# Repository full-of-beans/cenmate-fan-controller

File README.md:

# CENMATE 6-Bay HDD Enclosure Fan Controller

Custom cooling and power-monitoring controller for a **CENMATE six-bay USB HDD enclosure (JBOD/DAS)**.

> **CMFC001 prototype boards ordered (2026-11-20).** This is an engineering prototype, not a qualified assembled product. See [hardware revision register](docs/hardware-revisions.md) for the immutable KiCad/manufacturing source and order status.

## Current design

- **Controller:** Seeed Studio XIAO RP2350, powered from the enclosure's USB-A 5 V supply through its USB-C connector. Fan 12 V switching is controlled separately by the enclosure rocker via J5 and Q3, not by USB availability.
- **Fans:** Two independently controlled 12 V, four-wire PWM fans, with separate PWM drive and tachometer inputs. The intended physical fan headers are [MODDIY 2.54 mm right-angle 4-pin male fan connectors](https://www.moddiy.com/products/5408/4-Pin-3-Pin-2.54mm-Pitch-2510-Fan-Male-Angled-Connector-Black.html). **The PCB still uses Molex right-angle header footprints/3D models as placeholders; the MODDIY parts have not been physically verified against those holes or pin orientation.** Do not purchase/install the Molex parts based on the current CAD representation.
- **Fan power:** DMP3056L-7 P-channel MOSFET switches the 12 V fan branch; its gate is controlled by the enclosure rocker via J5 and defaults off if the switch lead opens. PWM duty mapping and safe startup/reset behavior require firmware and bench verification.
- **Temperature sensing:** Two on-board 10 kΩ NTC thermistors, each read on its own XIAO ADC input through a 10 kΩ pull-up.
- **Current monitor:** TI INA228 on I²C, sensing the HDD backplane's positive 12 V feed through a **1 mΩ Bourns shunt**. The fan supply branches before the shunt, so the shunt measures the HDD branch rather than fan current. Accuracy and Kelvin/landing resistance must be checked by calibration.
- **HDD power path:** Center-positive 12 V barrel input **J1** → shunt **RSH1** → Phoenix Contact two-position screw terminal **J2** → HDD enclosure. **J2 pin 1 = +12 V, pin 2 = GND.** The PCB has explicit `12V` and `GND` silkscreen markings beside J2; verify wiring polarity before connection.
- **Grounding:** Common system ground, with a two-layer PCB and ground copper fill.

The enclosure's power brick is labeled **12 V / 9 A**. The selected **Tensility 54-00286 barrel jack is rated 7 A**; the owner has explicitly accepted the prototype risk rather than replacing it. This does **not** establish that six-drive startup and operating loads meet the connector rating. Measure the actual current, contact voltage drop, and connector heating during controlled bring-up.

## Hardware and mechanical status

The board and custom backplate have been checked for fit by the owner in Onshape. This does not independently verify fabricated edge reliefs, actual mated MODDIY header geometry, cable bends, or as-built tolerances. Check physical fit before connecting the HDD enclosure.

The CMFC001 prototype PCB was ordered from JLCPCB as **25 bare 30 × 80 mm, two-layer, 1.6 mm FR-4, 1 oz copper, green-mask, lead-free HASL boards**, plus one top-side paste stencil (JLCPCB order `W2026112104450984`). Actual manufactured fit, CAM interpretation, and assembly remain to be checked when boards arrive.

## Repository layout

```text
hardware/
  fan-controller.kicad_pro   KiCad 10 project
  fan-controller.kicad_sch   Current controller schematic
  fan-controller.kicad_pcb   Current PCB layout
  fan-controller.kicad_dru   Custom DRC rules
  libraries/                 Project-local symbols, footprints, and models
firmware/                   Pico SDK firmware and native tests
docs/                       Circuit design and hardware revision records
mechanical/                 Mechanical files (as available)
```

Open `hardware/fan-controller.kicad_pro` with **KiCad 10**. The project-local `FanController` libraries must resolve before editing or plotting.

## Ordered prototype and validation

CMFC001 manufacturing identity, source commit and archive path are recorded in [hardware revisions](docs/hardware-revisions.md). Do not regenerate the ordered ZIP as part of documentation cleanup.

Before connecting drives, perform continuity and polarity checks, current-limited initial power-up, USB/12 V power sequencing, fan enable/PWM/tach tests, INA228 communication and calibration, and thermistor checks. Only then test with the enclosure under controlled startup/full-load conditions while monitoring the accepted 7 A connector risk.

## Firmware design status

Phase 1 adds USB configuration and telemetry, persistent independent FIXED PWM, electrical and rear-plenum sensing, and AUTO diagnostics and protective cooling. Factory AUTO uses 100% duty while the cooling model is uncalibrated. FIXED has no automatic cooling overrides and remains active at the selected duty if the host disconnects. Assembled hardware and autonomous thermal behavior await bench validation.

- [Firmware architecture and verified CAD pin mapping](docs/software-architecture.md)
- [Build, flash, bring-up and characterization](docs/hardware-bringup.md)
- [USB CDC protocol](docs/usb-protocol.md)
- [Configuration schema and persistence](docs/firmware-configuration.md)

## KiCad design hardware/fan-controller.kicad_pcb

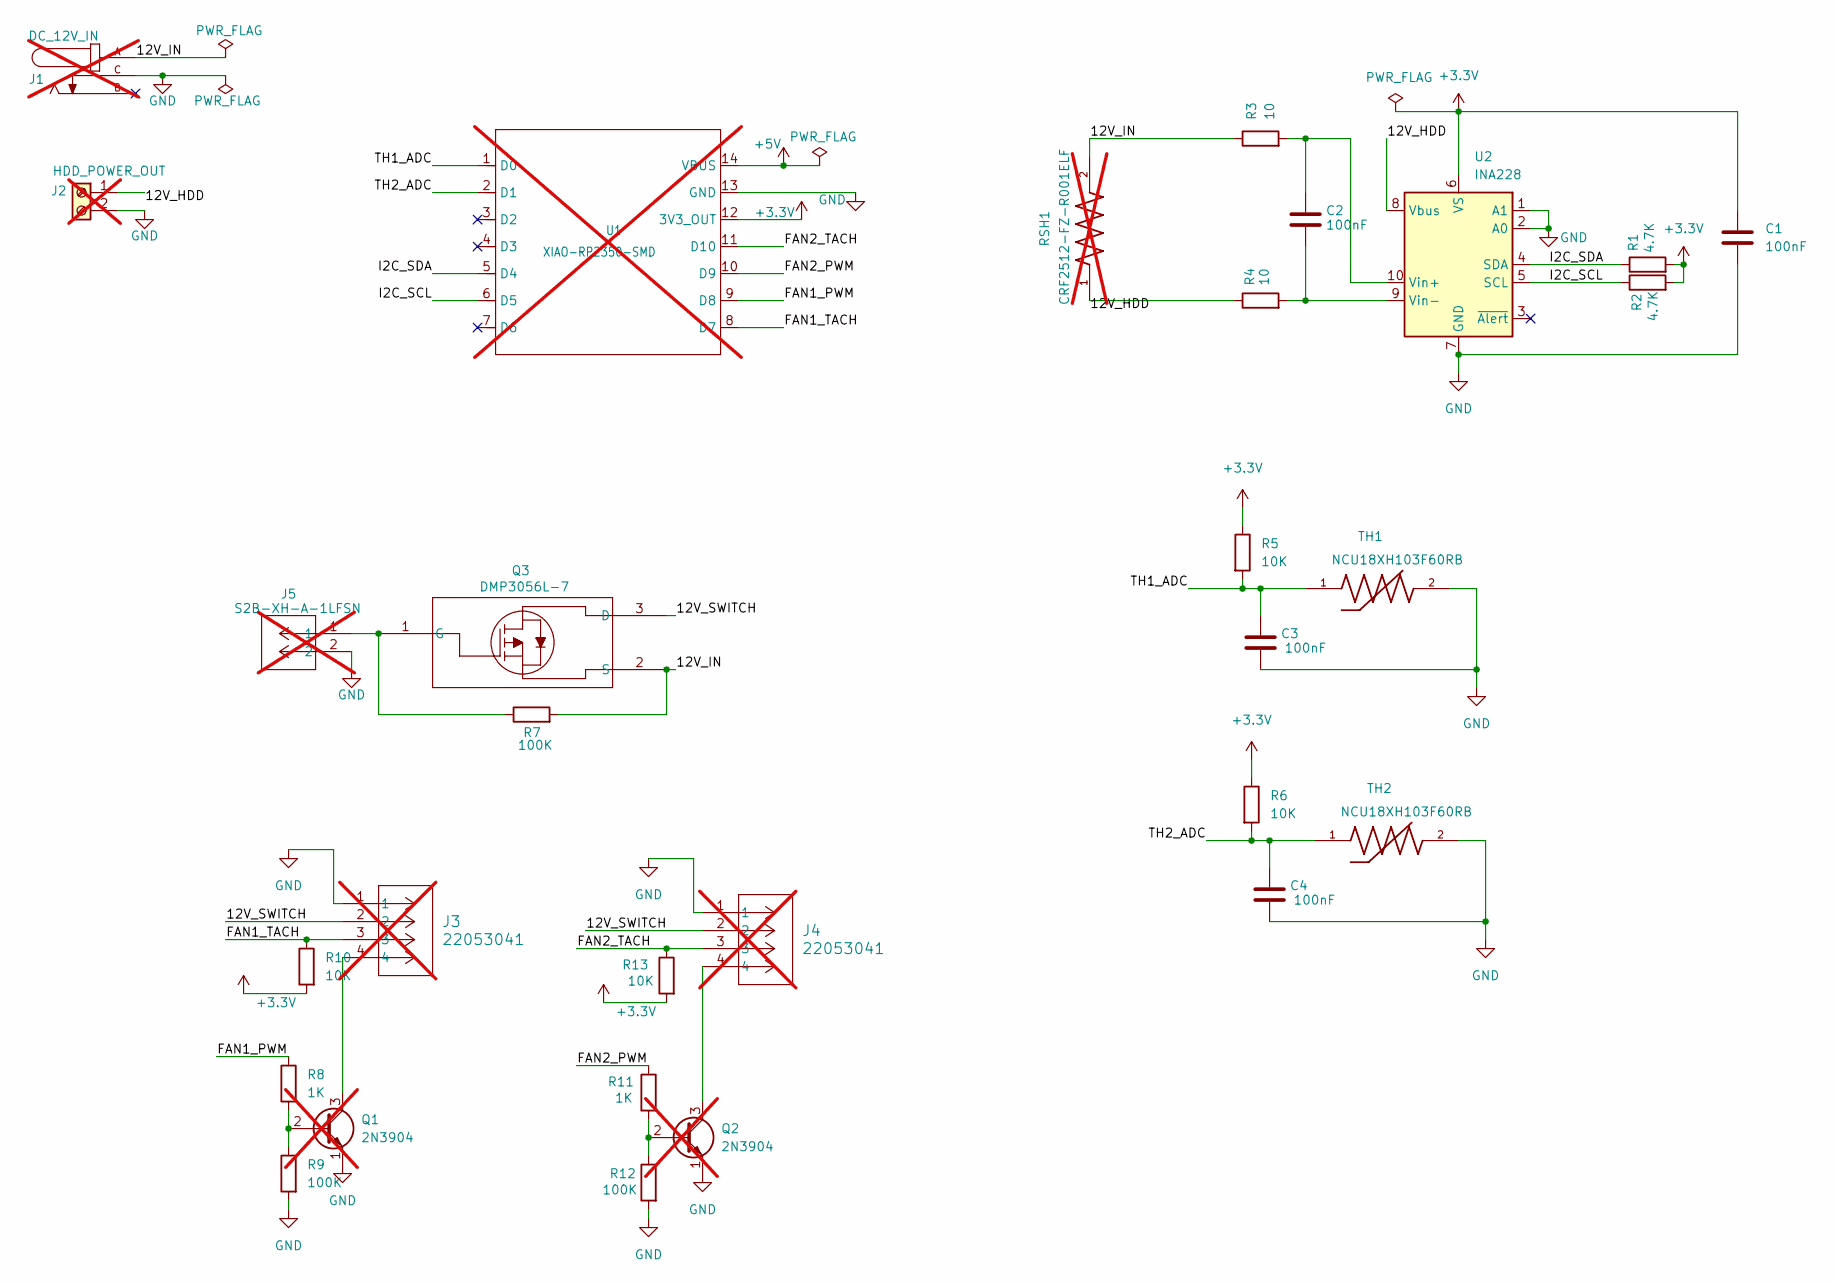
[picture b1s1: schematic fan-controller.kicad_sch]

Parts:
C1, C2, C3, C4: 100nF; C_0805_2012Metric; MPN CL21B104KACNFNC; DigiKey_PN 1276-2442-1-ND
J1: DC_12V_IN; TENSILITY_54-00286; MPN 54-00286; DigiKey_PN 839-54-00286-ND; not fitted
J2: HDD_POWER_OUT; PHOENIX_5442206; MPN 5442206; DigiKey_PN 277-12547-ND; not fitted
J3, J4: 22053041; CONN_A-7478-04A_MOL; MPN 0022053041; DigiKey_PN WM4302-ND; not fitted
J5: S2B-XH-A-1LFSN; CONN_S2B-XH-A-1LFSN_JST; MPN S2B-XH-A-1(LF)(SN); not fitted
Q1, Q2: 2N3904; TO-92_Inline; MPN 2N3904BU; DigiKey_PN 2N3904FS-ND; not fitted
Q3: DMP3056L-7; DIODE3_DESD1CAN2SOQ-7_DIO; MPN DMP3056L-7; DigiKey_PN DMP3056L-7DICT-ND
R1, R2: 4.7K; R_0805_2012Metric; MPN RC0805FR-074K7L; DigiKey_PN 311-4.70KCRCT-ND
R3, R4: 10; R_0805_2012Metric; MPN RC0805FR-0710RL; DigiKey_PN 311-10.0CRCT-ND
R5, R6, R10, R13: 10K; R_0805_2012Metric; MPN RC0805FR-0710KL; DigiKey_PN 311-10.0KCRCT-ND
R7, R9, R12: 100K; R_0805_2012Metric; MPN RC0805FR-07100KL; DigiKey_PN 311-100KCRCT-ND
R8, R11: 1K; R_0805_2012Metric; MPN RC0805FR-071KL; DigiKey_PN 311-1.00KCRCT-ND
RSH1: CRF2512-FZ-R001ELF; RESC6432X80N; MPN CRF2512-FZ-R001ELF; DigiKey_PN CRF2512-FZ-R001ELFCT-ND; not fitted
TH1, TH2: NCU18XH103F60RB; THRMC1608X95N; MPN NCU18XH103F60RB; DigiKey_PN 490-16279-1-ND
U1: XIAO-RP2350-SMD; XIAO-RP2350-no-underside; MPN 102010550; DigiKey_PN 1597-102010550-ND; not fitted
U2: INA228; TSSOP-10_3x3mm_P0.5mm; MPN INA228AIDGSR; DigiKey_PN 296-INA228AIDGSRCT-ND

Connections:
+3.3V: C1.1, R1.2, R2.2, R5.1, R6.1, R10.2, R13.2, U1.12 (3V3_OUT), U2.6 (VS)
+5V: U1.14 (VBUS)
/12V_HDD: J2.1, R4.1, RSH1.1, U2.8 (Vbus)
/12V_IN: J1.A, Q3.2 (S), R3.1, R7.2, RSH1.2
/12V_SWITCH: J3.2, J4.2, Q3.3 (D)
/FAN1_PWM: R8.1, U1.9 (D8)
/FAN1_TACH: J3.3, R10.1, U1.8 (D7)
/FAN2_PWM: R11.1, U1.10 (D9)
/FAN2_TACH: J4.3, R13.1, U1.11 (D10)
/I2C_SCL: R2.1, U1.6 (D5), U2.5 (SCL)
/I2C_SDA: R1.1, U1.5 (D4), U2.4 (SDA)
/TH1_ADC: C3.1, R5.2, TH1.1, U1.1 (D0)
/TH2_ADC: C4.1, R6.2, TH2.1, U1.2 (D1)
GND: C1.2, C3.2, C4.2, J1.C, J2.2, J3.1, J4.1, J5.2, Q1.1 (E), Q2.1 (E), R9.2, R12.2, TH1.2, TH2.2, U1.13 (GND), U2.1 (A1), U2.2 (A0), U2.7 (GND); also elsewhere on the board
unnamed: Q1.2 (B), R8.2, R9.1
unnamed: J3.4, Q1.3 (C)
unnamed: Q2.2 (B), R11.2, R12.1
unnamed: J4.4, Q2.3 (C)
unnamed: J5.1, Q3.1 (G), R7.1
unnamed: C2.1, R3.2, U2.10 (Vin+)
unnamed: C2.2, R4.2, U2.9 (Vin-)

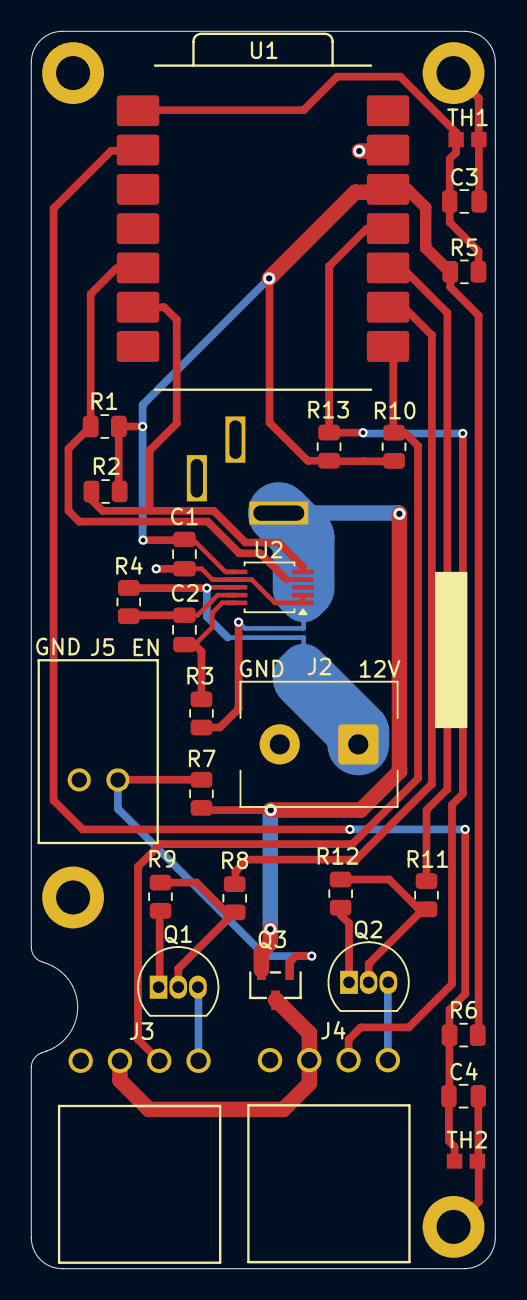
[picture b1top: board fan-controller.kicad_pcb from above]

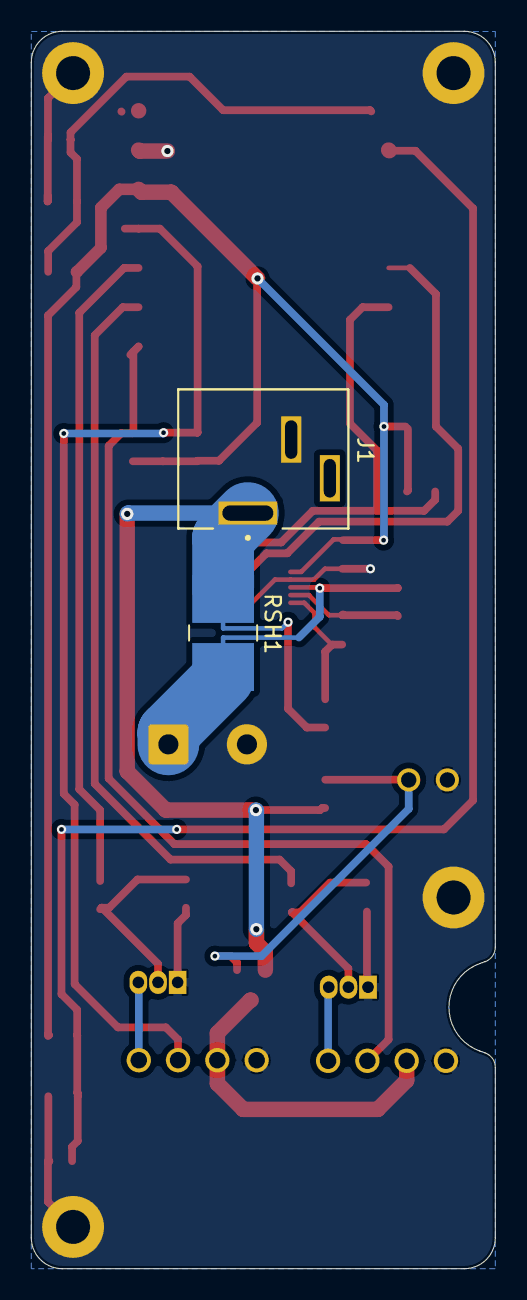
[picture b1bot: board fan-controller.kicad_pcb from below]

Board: 2 copper layers, 30.0 x 80.0 mm, 34 parts (2 on the bottom side), 20 nets.

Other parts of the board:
H1, H2, H3, H4: MountingHole_2.2mm_M2_Pad_4mm

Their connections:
GND: H1.1, H2.1, H3.1, H4.1; also elsewhere on the board

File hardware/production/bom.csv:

Designator,Footprint,Quantity,Value,LCSC Part #
"C1, C2, C3, C4",0805,4,100nF,CL21B104KACNFNC
Q3,DIODE3_DESD1CAN2SOQ-7_DIO,1,DMP3056L-7,DMP3056L-7
"R1, R2",0805,2,4.7K,RC0805FR-074K7L
"R10, R13, R5, R6",0805,4,10K,RC0805FR-0710KL
"R11, R8",0805,2,1K,RC0805FR-071KL
"R12, R7, R9",0805,3,100K,RC0805FR-07100KL
"R3, R4",0805,2,10,RC0805FR-0710RL
"TH1, TH2",THRMC1608X95N,2,NCU18XH103F60RB,NCU18XH103F60RB
U2,TSSOP-10_3x3mm_P0.5mm,1,INA228,INA228AIDGSR

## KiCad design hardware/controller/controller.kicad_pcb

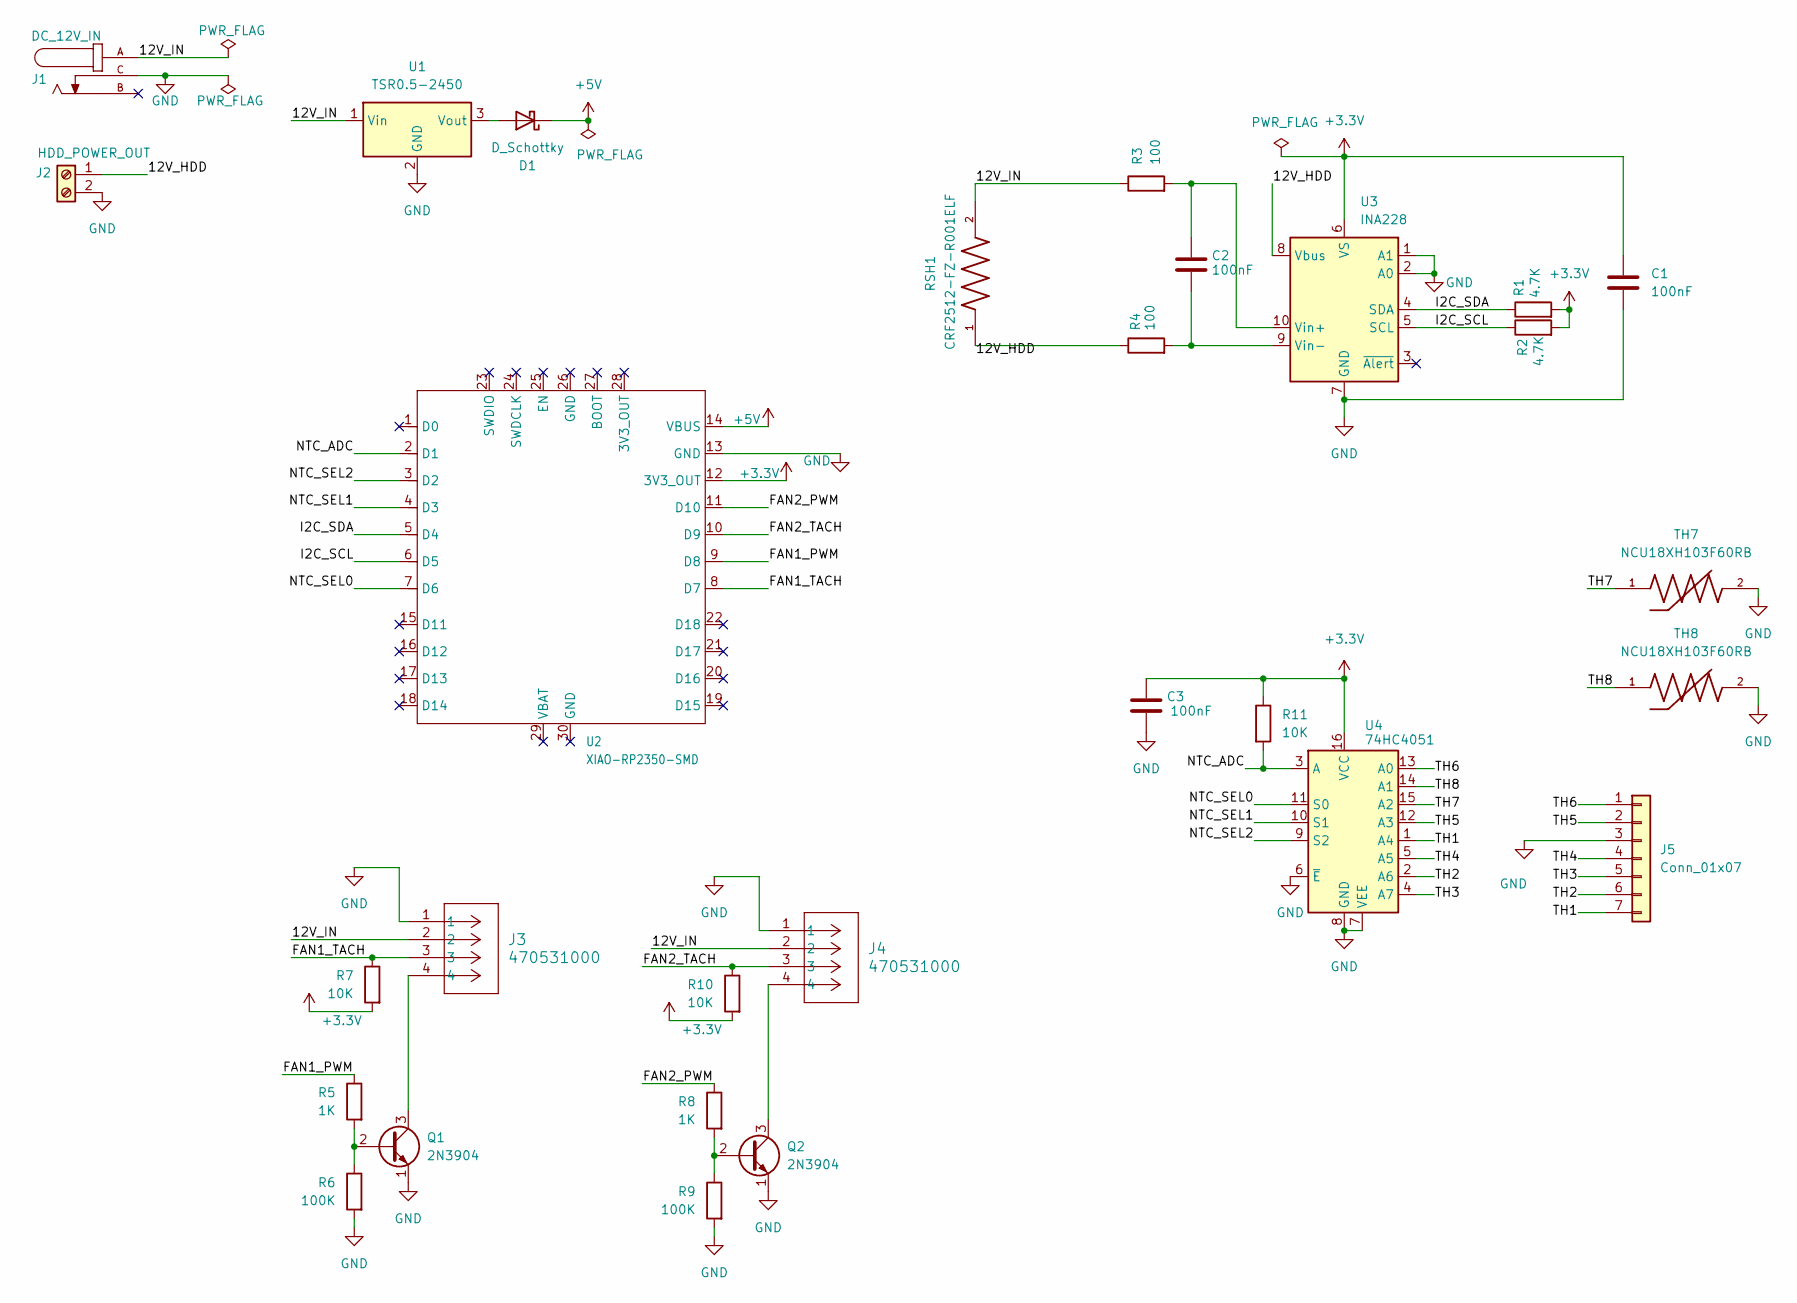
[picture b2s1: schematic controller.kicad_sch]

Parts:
C1, C2, C3: 100nF; C_0805_2012Metric
D1: D_Schottky; D_SOD-123F
J1: DC_12V_IN; TENSILITY_54-00286; PARTREV A
J2: HDD_POWER_OUT; TerminalBlock_Phoenix_MKDS-3-2-5.08_1x02_P5.08mm_Horizontal
J3, J4: 470531000; CONN_SD-47053-001_H10p00_MOL
J5: Conn_01x07; JST_ZH_B7B-ZR_1x07_P1.50mm_Horizontal
Q1, Q2: 2N3904; TO-92_Inline
R1, R2: 4.7K; R_0805_2012Metric
R3, R4: 100; R_0805_2012Metric
R5, R8: 1K; R_0805_2012Metric
R6, R9: 100K; R_0805_2012Metric
R7, R10, R11: 10K; R_0805_2012Metric
RSH1: CRF2512-FZ-R001ELF; RESC6432X80N
TH7, TH8: NCU18XH103F60RB; THRMC1608X95N
U1: TSR0.5-2450; Converter_DCDC_TRACO_TSR0.5-24xx_TSR0.5-24xxx_THT
U2: XIAO-RP2350-SMD; XIAO-RP2350-no-underside
U3: INA228; TSSOP-10_3x3mm_P0.5mm
U4: 74HC4051; SOIC-16_3.9x9.9mm_P1.27mm

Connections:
+3.3V: C1.1, C3.1, R1.2, R2.2, R7.2, R10.2, R11.1, U2.12 (3V3_OUT), U3.6 (VS), U4.16 (VCC)
+5V: D1.1 (K), U2.14 (VBUS)
/12V_HDD: J2.1, R4.1, RSH1.1, U3.8 (Vbus)
/12V_IN: J1.A, J3.2, J4.2, R3.1, RSH1.2, U1.1 (Vin)
/FAN1_PWM: R5.1, U2.9 (D8)
/FAN1_TACH: J3.3, R7.1, U2.8 (D7)
/FAN2_PWM: R8.1, U2.11 (D10)
/FAN2_TACH: J4.3, R10.1, U2.10 (D9)
/I2C_SCL: R2.1, U2.6 (D5), U3.5 (SCL)
/I2C_SDA: R1.1, U2.5 (D4), U3.4 (SDA)
/NTC_ADC: R11.2, U2.2 (D1), U4.3 (A)
/NTC_SEL0: U2.7 (D6), U4.11 (S0)
/NTC_SEL1: U2.4 (D3), U4.10 (S1)
/NTC_SEL2: U2.3 (D2), U4.9 (S2)
/TH1: J5.7, U4.1 (A4)
/TH2: J5.6, U4.2 (A6)
/TH3: J5.5, U4.4 (A7)
/TH4: J5.4, U4.5 (A5)
/TH5: J5.2, U4.12 (A3)
/TH6: J5.1, U4.13 (A0)
/TH7: TH7.1, U4.15 (A2)
/TH8: TH8.1, U4.14 (A1)
GND: C1.2, C3.2, J1.C, J2.2, J3.1, J4.1, J5.3, Q1.1 (E), Q2.1 (E), R6.2, R9.2, TH7.2, TH8.2, U1.2 (GND), U2.13 (GND), U3.1 (A1), U3.2 (A0), U3.7 (GND), U4.6 (~E), U4.7 (VEE), U4.8 (GND)
unnamed: D1.2 (A), U1.3 (Vout)
unnamed: Q1.2 (B), R5.2, R6.1
unnamed: J3.4, Q1.3 (C)
unnamed: Q2.2 (B), R8.2, R9.1
unnamed: J4.4, Q2.3 (C)
unnamed: C2.1, R3.2, U3.10 (Vin+)
unnamed: C2.2, R4.2, U3.9 (Vin-)

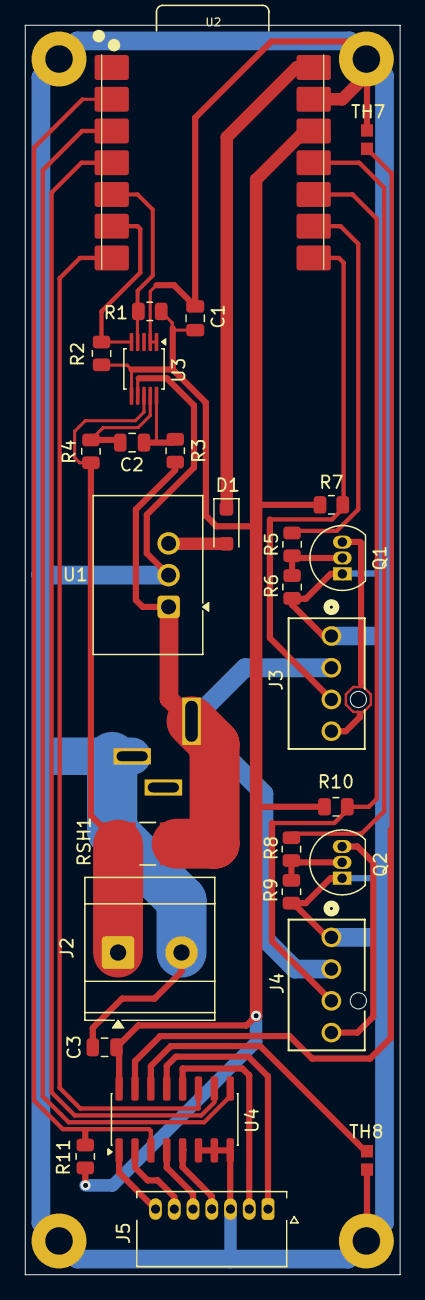
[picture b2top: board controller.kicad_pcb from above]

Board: 2 copper layers, 30.0 x 100.0 mm, 29 parts (1 on the bottom side), 30 nets.

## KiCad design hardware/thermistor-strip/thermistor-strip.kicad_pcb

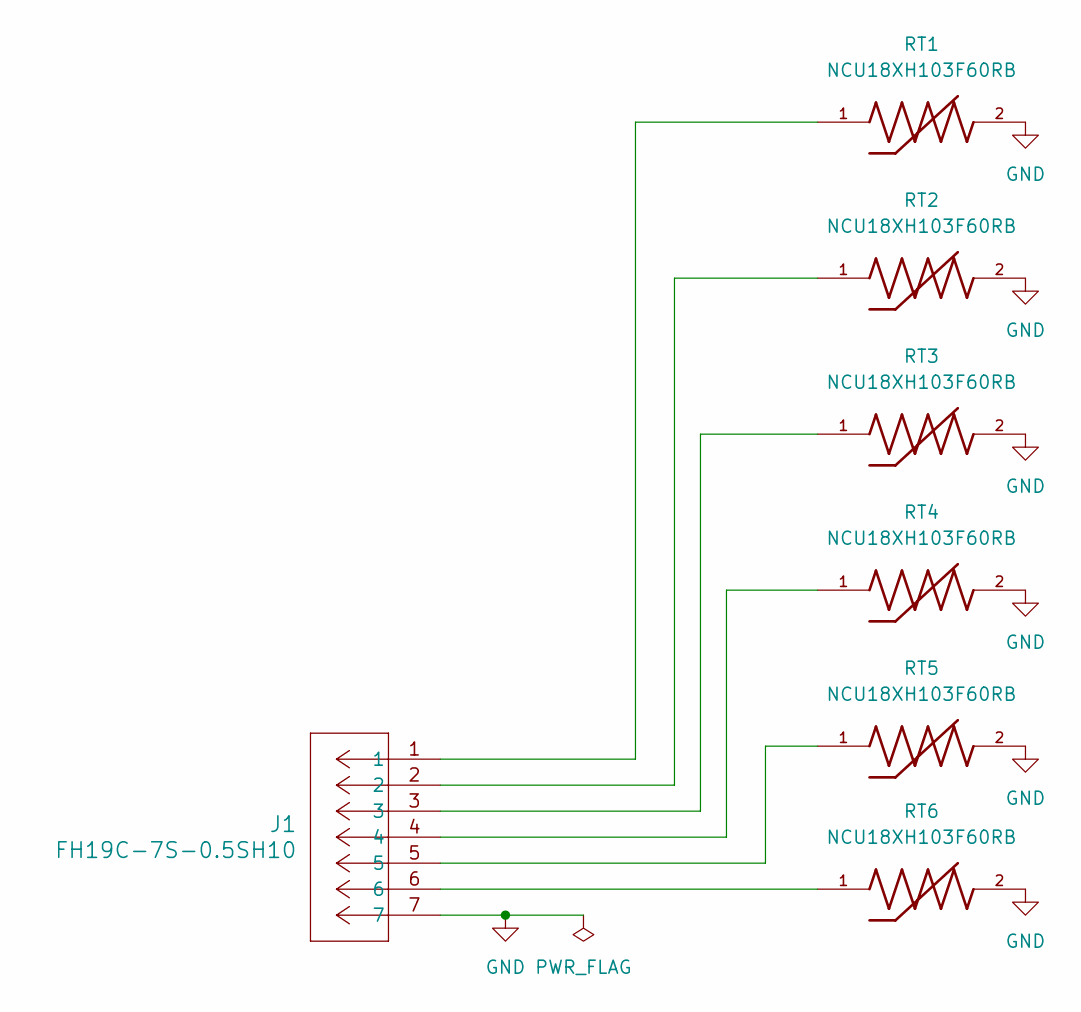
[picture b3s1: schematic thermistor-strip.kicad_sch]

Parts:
J1: FH19C-7S-0.5SH10; CONN7_FH19C_7S_HIR
RT1, RT2, RT3, RT4, RT5, RT6: NCU18XH103F60RB; THRMC1608X95N

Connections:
GND: J1.7, RT1.2, RT2.2, RT3.2, RT4.2, RT5.2, RT6.2
unnamed: J1.1, RT1.1
unnamed: J1.2, RT2.1
unnamed: J1.3, RT3.1
unnamed: J1.4, RT4.1
unnamed: J1.5, RT5.1
unnamed: J1.6, RT6.1

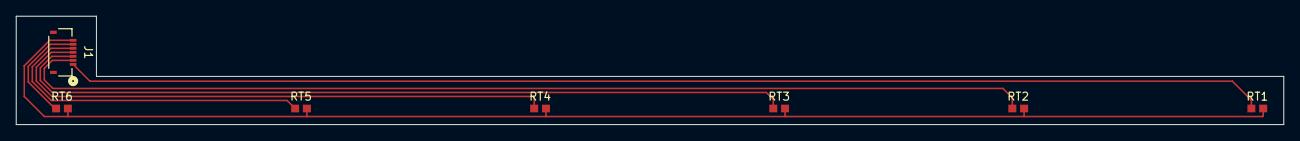
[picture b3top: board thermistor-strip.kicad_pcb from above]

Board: 2 copper layers, 158.0 x 13.5 mm, 7 parts (0 on the bottom side), 7 nets.
